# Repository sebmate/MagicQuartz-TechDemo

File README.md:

# MagicQuartz Turntable Speedbox

## Introduction

This repository contains an open source hardware design of a turntable speedbox that is capable of running the [MagicQuartz](https://www.mate-labs.de/magicquartz) firmware. The hardware design consists of two parts:

* An [OpenSCAD](https://openscad.org) model that can be used for generating a 3D-printable enclosure.
* A [KiCad](https://www.kicad.org) design for the mainboard, comprising schematic and PCB.

The speedbox implements an AC power inverter based on a class-D audio amplifier and a toroidal transformer to step-up the voltage. The speed of the record player is controlled by changing the generated AC frequency. This enables electronic switching between the standard record speeds (16, 33, 45, and 78 RPM) and real-time speed correction using an optical sensor. Note that this approach only works for turntables with AC motor. Optional voltage reduction can significantly reduce motor noise on synchronous motors.

The device supports the most important features of MagicQuartz version 1.1x, "Sparrow", including the "Advanced Power Management" (APM). However, it lacks standby for the LCD backlight and fans and it does not implement hardware-side pop supression.

## Licensing

The information and files in this repository are provided under the [CERN-OHL-S v2](cern_ohl_s_v2.txt) open source license (please click [here](https://ohwr.org/project/cernohl/wikis/Documents/CERN-OHL-version-2) for details).

## Hardware Design

### Safety & Disclaimer

In the hardware design presented here, great emphasis was put on safety. For example, the housing features active cooling and touch protection. It creates an IT network (Isolé Terre). The circuitry is equipped with safeguards against overcurrent and overvoltage (the latter with the LittleJimmy extension, see below). Finally, the MagicQuartz firmware implementes further safety measures in software (see documentation).

However, the main purpose of this repository is to provide an easily reproducible, simple hardware design to demonstrate the capabilities of the MagicQuartz firmware (this is why it is called "TechDemo"). The design has not been formally tested for electrical safety, electromagnetic compatibility (EMC), or fire safety. If you build and/or operate the device, you do so at your own risk. If you do not have sufficient knowledge in electronics, please do not attempt to build and/or operate the device. Also pay close attention to section 6 of the [CERN-OHL-S v2](cern_ohl_s_v2.txt) license and the safety considerations below. Devices manufactured based on this design may not be suitable for end users.

The following is a list of safety considerations that you should keep in mind:

* The device is capable of generating high voltage and may cause fire and/or serious injury, including death.
* The device switches high currents using pulse width modulation (PWM), which may cause interference with other electronic devices or radio equipment.
* Be careful when performing measurements. There is (generally) no need to measure the generated sine signal on the high-voltage side of the transformer using an oscilloscope, as this can also be done on the low-voltage side. In this regard, also note that the digital amplifier's negative outputs are not connected to ground. There is a risk of damaging the oscilloscope and other equipment when performing measurements while the circuit is grounded, e.g. over the Arduino's USB port and a PC.
* A fully insulated power supply must be used to create an IT network (Isolé Terre).
* There is a small but potential risk that the speedbox could damage connected devices due to overvoltage. This may happen, for example, if the speedbox is improperly set-up or if the connected device contains sensitive electronics. Also note that although software-based pop suppression is implemented in the MagicQuartz firmware, a voltage spike may occur when the device is switched on. For this reason, the speedbox should be switched on before the turntable. Note that no damage has been reported to date.
* The individual prefabricated modules (especially the amplifier, the step-down converters and the microcontroller board) may contain electronic components from different manufacturers and of varying quality (see section "Known Issues"). In the event of a hardware failure, this could lead to further damage. The assembled device should therefore never be operated unattended.
* Note that the mechanical, electrical, and chemical properties of 3D-printed parts may change or deteriorate over time.

### OpenSCAD 3D Model

The OpenSCAD file can be used to virtually explore the device and to 3D-print a physical enclosure.

*Note:* If the symbols on the front are not displayed correctly, the "Symbola" font has to be installed (Ubuntu package name: `fonts-symbola`).

#### Parts Overview and Printing Notes

The table below provides an overview of all 3D-printable parts in the 3D model along with some notes. Be aware that the printing time in total is around 22 hours (on an Ultimaker 2).

While the STL files are available in the `release` folder for your convenience, they can be generated easily in OpenSCAD. Set the variable `render_components` to `false` and change the value of the variable `generate` to the respective part number. Then press F5 to preview the part, F6 to render the part, and F7 to export the STL file. Note that the rendering process may take a considerable amount of time, even on fast computers. Also note that the generated objects are already properly oriented for printing.

I had some problems printing with Cura versions 5.1.1 to 5.3.0, especially with the "Back" part. The slicer created some signifcant artifacts and did not handle the text as expected (the last layer under the text was not printed as expected). I went back to 4.13.1.

In addition to the table below:

* Print all parts using "tree" support.
* Print all parts using the "grid" infill pattern (except part 3, see notes).
* Print all parts with with 0.2 mm layer height (except part 8, see notes).
* Print all parts with with adhesion type "brim" (except part 8, see notes).

| Part Nr. | Name                          | Suggested Color | Notes / Exceptions                                                                                                       |
|----------|-------------------------------|-----------------|--------------------------------------------------------------------------------------------------------------------------|
| 1        | Bottom Plate                  | Black           | May be printed without "tree" support.                                                                                   |
| 1        | Bottom Plate (Material Saver) | Black           | Saves some filament, but is less sturdy. May be printed without "tree" support.                                          |
| 2        | Front Lower Part              | White           | Set "Support X/Y Distance" to 1.6 mm to prevent the slicer from creating support in the air inlet.                       |
| 3        | Front Center Part             | Transparent     | Use the "lightning" infill pattern to create a nice "quartz-like" appearance.                                            |
| 4        | Front Upper Part              | White           |                                                                                                                          |
| 5        | Cover                         | Brown           | Print this variant if you do not plan to apply decorative foil.                                                          |
| 5        | Cover (Material Saver)        | (Any)           | If decorative foil does not adhere properly to the edges, slightly sand down the surfaces at the edges.                  |
| 6        | Foot (Print 4x)               | Silver          | May be printed without "brim".                                                                                           |
| 7        | Voltmeter Cover               | As Front        |                                                                                                                          |
| 8        | Button Assembly               | Silver          | Print with 0.1 mm or less to improve strength, do not use adhesion support (brim). Enable ironing on top layer.          |
| 9        | Back                          | White           |                                                                                                                          |
| 10       | Dummy sockets                 | As Back         | Print without "brim".                                                                                                    |
| 11       | Optical Sensor Case           | Black           |                                                                                                                          |

#### Components
The components to be used should be easily identifiable from the OpenSCAD and KiCad projects. For components where this is not immediately obvious, here are some details:

* **Screws:** All parts can be held together with self-tapping screws type "DIN 7981 C H", 2.9x9.5 mm, except for the LCD and voltmeter cover, where 2.2x9.5 mm should be used. The DIN screws can of course also be substituted with similar compatible screws.
* **Cable Ties:** The enclosure has been designed to mount various components with cable ties, such as the transformer, the internal fan (only used for amplifier type 2), the high-voltage screw terminal, and to secure the AC out cable. The bar in the center of the enclosure can be used to attach wires with cable ties.
* **Amplifiers:** The OpenSCAD design currently supports the accommodation of two types of digital power amplifier boards based on the TDA7498 and TPA3116D2 chips, respectively (see renderings below). The first type seems to be very fragile and requires about 28V. The second type is more robust and works well at 24V, but has more noise and definitely needs a better heatsink. However, it is possible to modify the design to accommodate other types. There is also a third "placeholder" type that can be used for custom developments.
* **Toroidal Transformer:** Type "RKT 5012" (50VA, 220V to 2x12V). To distribute the load across both amplifier channels, the two 12V transformer windings can be driven in parallel via the two output channels of the amplifier. It is then important to ensure that the two windings are actually driven in parallel and not in reverse. Given a connection sequence of "R+, R-, L+, L-" at the amplifier, a working wiring sequence is "red, yellow, blue, green" for the RKT 5012. Caution! During operation, the 220V tappings are live.
* **AC Voltmeter:** Type "YB27A", 60-300V AC, removed from its original housing. Note that the voltmeter is live and there is a risk of electric shock. If the wires need to be extended or replaced, make sure they have the proper voltage rating.
* **Power Switch:** Type "KCDI-101".
* **DC/DC Converter Boards:** Step-down voltage regulator boards based on the LM2596S (also see "Known Issues" below).
* **Fuses**: Fuse 1 covers the entire circuit and should be sized according to the implemented power rating. For example, if a 50VA transformer and a 24V power supply are used, a 2A fuse may be appropriate. Fuse 2 is used to protect the components on and connected to the "MEGA 2560 PRO" board, which draw approximately 100mA at 7.5V. Using a 125mA fast-acting fuse is therefore reasonable.

### KiCad Schematic and PCB

This repository also contains an electronic circuit for a mainboard. The PCB was designed for rapid prototyping and can be produced single-sided, e.g. with a small CNC or by etching. However, an optional top copper layer can be used to improve shielding. Of course, the PCB can also be manufactured by any PCB manufacturer.

The mainboard is build around the "MEGA 2560 PRO" board (denoted U1 in the schematic). To the author's knowledge, this board was originally developed by RobotDyn. Unfortunately, it seems to be no longer available, but re-makes by other companies are widely available. Click [here](https://robotdyn.com/mega-2560-pro-embed-ch340g-atmega2560-16au.html) for an archived version of RobotDyn's webpage.

The electronic circuit is very simple and should be self-explanatory. However, the following points explain some special aspects:

* **Power Supply:** Connector J2 ("Power") is used to power the mainboard from an external power source via pins 2 and 3 (typically 24-32V, depending on the voltage requirements of the amplifier, labeled "+24V" in the schematic). Connector J2 is also used to power the amplifier board via pins 1 and 4. Notice that pin 1 of J2 is connected to a second ground (GND1), which is used to measure the amplifier current (see below).
* **DC/DC Converter Boards:** As described above, the mainboard is supplied with 24-32V (labeled "+24V"). The U1 board, however, requires a voltage between 7V and 12V (labeled "+7.5V"). Because it is not practical to overcome the large voltage difference with a linear regulator, connector J3 ("DC/DC") can be used to connect an external DC/DC step-down converter board (see OpenSCAD design). U1 then uses its on-board linear voltage regulator (AMS1117) to create the 5V. The enclosure can accommodate a second DC/DC converter board specifically to power the fans; however, if the fans run well with the voltage from the first board, they can also be connected to this first converter board.
* **Jumper "Enable APM":** Digital pin D27 of U1 can be pulled to GND (jumper J1 "Enable APM" is closed) to tell the firmware that the current sensing circuit is available, which allows the firmware to detect whether the turntable motor is currently powered or not.
* **Current Measurement:** The current measurement works as follows: The current of the power section (the digital amplifier board) is measured via the voltage drop across resistor R4 (0.15 Ohm, 3W). The measured voltage is low-pass filtered via C7 and R5 and brought via U2A to a voltage level that can be easily measured by the microcontoller's ADC. 
* **Low-Pass Filter:** The PWM low-pass filter section converts the PWM signals from the microcontroller into one or two analog sine waves using simple RC filters. The filters are designed to have a cutoff frequency of about 200 Hz, which is high enough to pass any of the possible AC frequencies but block the PWM carrier signal. The filter is implemented twice in case a dual-phase inverter is to be implemented (which requires an additional transformer and a different enclosure). For single-phase configurations, it is recommended to equip only one filter section and bridge the two channels at the input of the amplifier. This eliminates the risk of damaging the amplifier if the user accidentally changes the phase shift in the firmware.

### Block Diagram

Here is a block diagram that provides an overview of all internal connections:

## Known Issues

### AMS1117 Voltage Regulator

The "MEGA 2560 PRO" board may use an "AMS1117" 5V voltage regulator of questionable quality (see [this](https://goughlui.com/2021/03/27/note-linear-regulator-woes-when-is-an-ams1117-not-an-ams1117) interesting blog post). The regulator may fail with a full or partial internal short and pass the input voltage (7.5V) to the rest of the circuit. This may not only damage the other components (including the ATmega2560), it may also increase the level of the sinusoidal signal generated. As a result, the inverter may generate excessive voltage and damage the turntable.

The problem can be overcome by replacing the AMS1117 by another "1117"-type regulator from a renowned manufacturer, such as the LM1117 by Texas Instruments or the TS1117 by Taiwan Semiconductor. Of course, the part should be purchased from a reputable electronics distributor. The old regulator can be desoldered easily by applying excess fresh solder to its three pins, heating everything up, and then wiping it away with the soldering iron.

Depending on the regulator, additional 10uF tantalum capacitors may need to be added to the input and output of the regulator (see data sheet). Such a modification based on an TS1117 is shown in this image: [images/TS1117-Modification.jpg](images/TS1117-Modification.jpg). Notice the two new yellow tantalum capacitors and the additional fuse (see below). Carefully observe the polarity of the capacitors!

A more sophisticated (and probably over-the-top) solution is adding a crowbar circuit and a fuse to the design. The crowbar circuit can be supplied as a small piggyback board for the "MEGA 2560 PRO". Such an add-on is available here: [https://github.com/sebmate/LittleJimmy](https://github.com/sebmate/LittleJimmy). Here is a picture of it mounted in the speedbox: [images/LittleJimmy.jpg](images/LittleJimmy.jpg).

The fuse is actually only needed for the crowbar circuit, but there is nothing wrong with adding it in general. The above block diagram and the rear panel of the enclosure have already been extended to incorporate this fuse. As described above, as the circuit is drawing about 100mA at 7.5V, using a 125mA fast-acting fuse is reasonable.

### LM2596S DC/DC Converter Boards

These inexpensive step-down boards probably don't use original LM2596S ICs (see [this](https://k6jca.blogspot.com/2018/02/counterfeit-lm2596-regulator-boards.html) link for more information). So far, however, I have had no issues with these. The above described crowbar circuit, when installed on the "MEGA 2560 PRO" board, also provides some protection against a possible failure of such an LM2596S DC/DC converter board.

## Parts Lists

Parts lists are available in the directory `parts-lists`.

One of the lists is for the German electronics distributor Reichelt. This list can also be accessed directly via this link: [https://www.reichelt.de/my/2038407](https://www.reichelt.de/my/2038407). This list also contains alternative parts that are not essential. The list should therefore not be ordered blindly. Please note that I am not affiliated with Reichelt and am only providing this list for your convenience. The parts may be available from other vendors at a lower price.

## Assembly Notes

* Assume that the assembly will take about two evenings, once you have all parts in place.
* The combination of mainboard and display can be fully tested without anything else being connected to it (such as the cabling to the rear panel, the amplifier, the DC/DC converter). This works by powering the "MEGA 2560 PRO" board via USB.
* Manual wiring of the display is very time-consuming. You may prefer to use a connector-based solution. Note that not all 16 display lines are required.
* Before connecting and powering the mainboard and the fans via the DC/DC converters, it is essential to set the voltages on them beforehand (e.g., to 7.5V, as described above).
* The specified screw for the fuse holder may be too long and may break through the rear panel. Be careful when mounting the fuse holder and consider using a shorter screw.
* Pictures of an assembled device are available in the `images` folder. Note that these do not yet show the latest revision with the LittleJimmy circuit and the second fuse.

## Initialization Procedure

The following steps describe how to initially setup the device:

* Before turning on the power for the first time, turn the amplifier board volume control all the way down.
* Follow the instructions in Section 4, "Getting Started", of the MagicQuartz documentation for flashing the firmware and executing the motor setup.
* When the "Motor Setup" routine asks you about the wave form (parameter `WaveForm`), set this to 2.
* When it comes to setting the voltage (parameter `VoltageMtOn`), the documentation says that the steps depend on whether the inverter installed in the speedbox has a level control or not. It has: it's the volume control of the amplifier. Proceed as described in the documentation: Set `VoltageMtOn` to 1, then slowly and carefully turn up the volume control of the amplifier until the desired voltage (e.g., 220V) is reached. If the amplifier switches into the protection state, try again.
* The inverter shutdown detection can be tested as described in section 4.3 of the software documentation by setting a too low `RampingSpeed` value and then restarting the inverter. If it does not work and if the measured current values in the firmware are on the lower end of the measuring range (which is from 0 to 1023), you may replace R7 with a higher value resistor, such as 470 kOhm.

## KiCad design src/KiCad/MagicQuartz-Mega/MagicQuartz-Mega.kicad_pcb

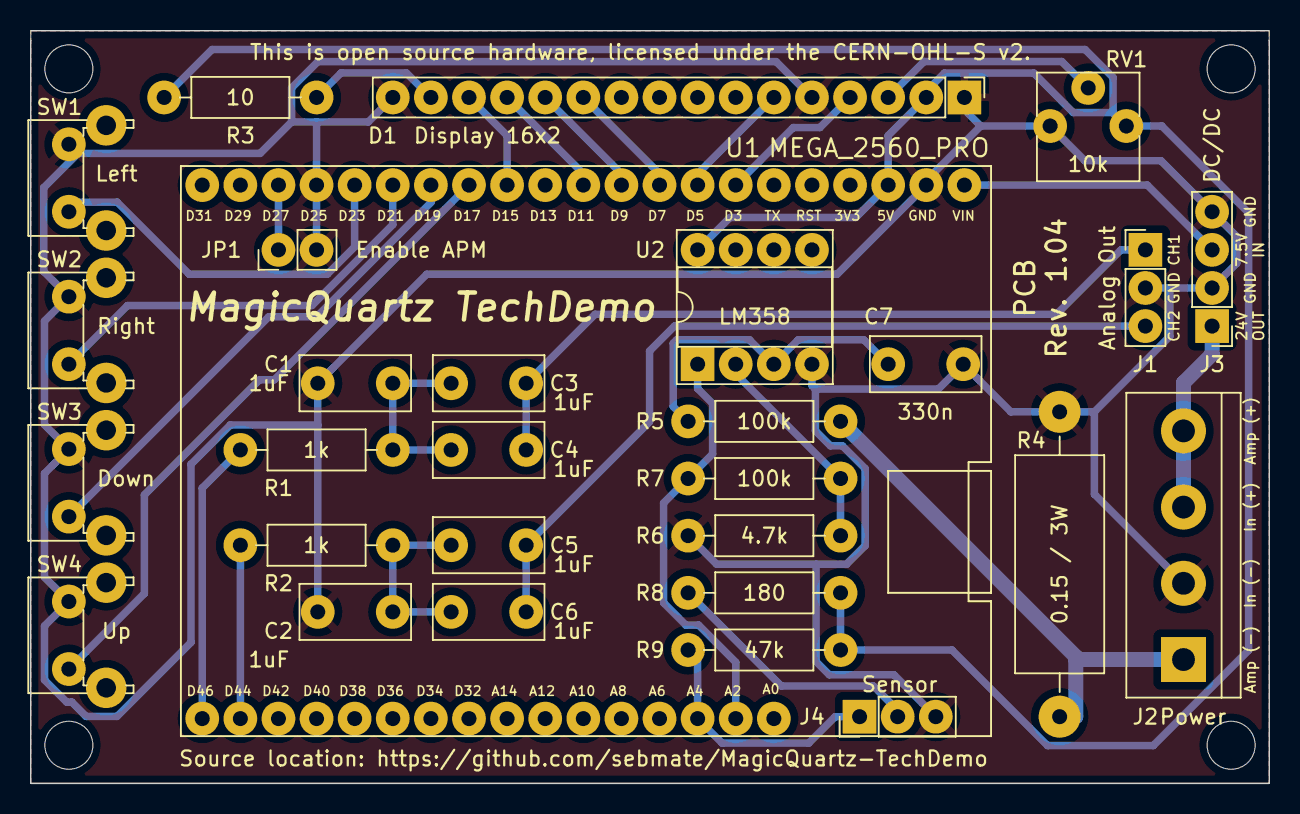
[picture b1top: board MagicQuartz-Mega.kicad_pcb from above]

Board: 2 copper layers, 82.6 x 50.2 mm, 33 parts (0 on the bottom side), 29 nets.

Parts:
C1, C2, C3, C4, C5, C6: 1uF; C_Rect_L7.2mm_W3.5mm_P5.00mm_FKS2_FKP2_MKS2_MKP2
C7: 330n; C_Rect_L7.2mm_W3.5mm_P5.00mm_FKS2_FKP2_MKS2_MKP2
D1: Display 16x2; PinHeader_1x16_P2.54mm_Vertical
H1, H2, H3, H4: MountingHole_Pad; MountingHole_3.2mm_M3
J1: Analog Out; PinHeader_1x03_P2.54mm_Vertical
J2: Power; TerminalBlock_bornier-4_P5.08mm
J3: DC/DC; PinHeader_1x04_P2.54mm_Vertical
J4: Sensor; PinHeader_1x03_P2.54mm_Vertical
JP1: Enable APM; PinHeader_1x02_P2.54mm_Vertical
R1, R2: 1k; R_Axial_DIN0207_L6.3mm_D2.5mm_P10.16mm_Horizontal
R3: 10; R_Axial_DIN0207_L6.3mm_D2.5mm_P10.16mm_Horizontal
R4: 0.15 / 3W; R_Axial_DIN0614_L14.3mm_D5.7mm_P20.32mm_Horizontal
R5, R7: 100k; R_Axial_DIN0207_L6.3mm_D2.5mm_P10.16mm_Horizontal
R6: 4.7k; R_Axial_DIN0207_L6.3mm_D2.5mm_P10.16mm_Horizontal
R8: 180; R_Axial_DIN0207_L6.3mm_D2.5mm_P10.16mm_Horizontal
R9: 47k; R_Axial_DIN0207_L6.3mm_D2.5mm_P10.16mm_Horizontal
RV1: 10k; Potentiometer_Vishay_T73YP_Vertical
SW1: Left; SW_Tactile_SPST_Angled_PTS645Vx83-2LFS
SW2: Right; SW_Tactile_SPST_Angled_PTS645Vx83-2LFS
SW3: Down; SW_Tactile_SPST_Angled_PTS645Vx83-2LFS
SW4: Up; SW_Tactile_SPST_Angled_PTS645Vx83-2LFS
U1: MEGA_2560_PRO; MEGA2560PRO-Reduced
U2: LM358; DIP-8_W7.62mm_Socket

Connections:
+5V: D1.2 (VDD), R3.2, R8.2, R9.2, RV1.1, U1.5V@1, U2.8 (V+)
+7.5V: J3.3, U1.VIN@1
+24V: J2.3, J2.4, J3.1
/Btn_Down: SW3.1, U1.D19
/Btn_Left: SW1.1, U1.D23
/Btn_Right: SW2.1, U1.D21
/Btn_Up: SW4.1, U1.D17
/Disp_D4: D1.11 (DB4), U1.D7
/Disp_D5: D1.12 (DB5), U1.D9
/Disp_D6: D1.13 (DB6), U1.D11
/Disp_D7: D1.14 (DB7), U1.D15
/Disp_E: D1.6 (E), U1.D5
/Disp_RS: D1.4 (RS), U1.D3
/OUT1: C3.1, C4.1, J1.1
/OUT2: C5.1, C6.1, J1.3
/PWM_1: R1.2, U1.D46
/PWM_2: R2.2, U1.D44
/Power_Sense: R7.2, U1.A2, U2.1
/Sensor: J4.1, R9.1, U1.A4
GND: C1.2, C2.2, C7.2, D1.1 (VSS), D1.5 (R/W), D1.16 (LED-), J1.2, J2.2, J3.2, J3.4, J4.3, JP1.2 (B), R4.1, R6.1, RV1.3, SW1.2, SW2.2, SW3.2, SW4.2, U1.D25, U1.GND@1, U2.4 (V-)
GND1: J2.1, R4.2, R5.2
unnamed: C1.1, C3.2, C4.2, R1.1
unnamed: C2.1, C5.2, C6.2, R2.1
unnamed: C7.1, R5.1, U2.3 (+)
unnamed: D1.3 (VO), RV1.2
unnamed: D1.15 (LED+), R3.1
unnamed: J4.2, R8.1
unnamed: JP1.1 (A), U1.D27
unnamed: R6.2, R7.1, U2.2 (-)

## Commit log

2023-01-09 Files for Release 1.02
2023-01-10 Update documentation
2023-03-08 Add files
2023-03-23 Update images
2023-03-23 Update files in release folder. Do not use ZIP.
2023-03-23 Cleanup old files
2023-03-27 Add pictures of assembled device
2023-03-27 Add parts lists
2023-05-04 Add more sturdy bottom plate (not "material saver")
2023-05-09 Add zener diode protection for potential AMS1117 failure.
2023-05-09 Update block diagram
2023-05-22 Add image showing the TS1117 modification
2023-05-22 Remove old image
2023-05-22 Update README.md on AMS1117 issue
2023-05-22 Update parts list
2023-05-22 Add image
2023-07-29 Update to 1.04
    Clarify voltages and update documentation
2023-07-29 Add +24V to HighPower net
2023-08-14 Update documentation
    Update info regarding the crowbar circuit
2025-09-16 Add firmware files
2025-09-16 Fix README.md

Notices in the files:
src/KiCad/MagicQuartz-Mega/MagicQuartz-Mega.kicad_pcb:
This is open source hardware, licensed under the CERN-OHL-S v2.
